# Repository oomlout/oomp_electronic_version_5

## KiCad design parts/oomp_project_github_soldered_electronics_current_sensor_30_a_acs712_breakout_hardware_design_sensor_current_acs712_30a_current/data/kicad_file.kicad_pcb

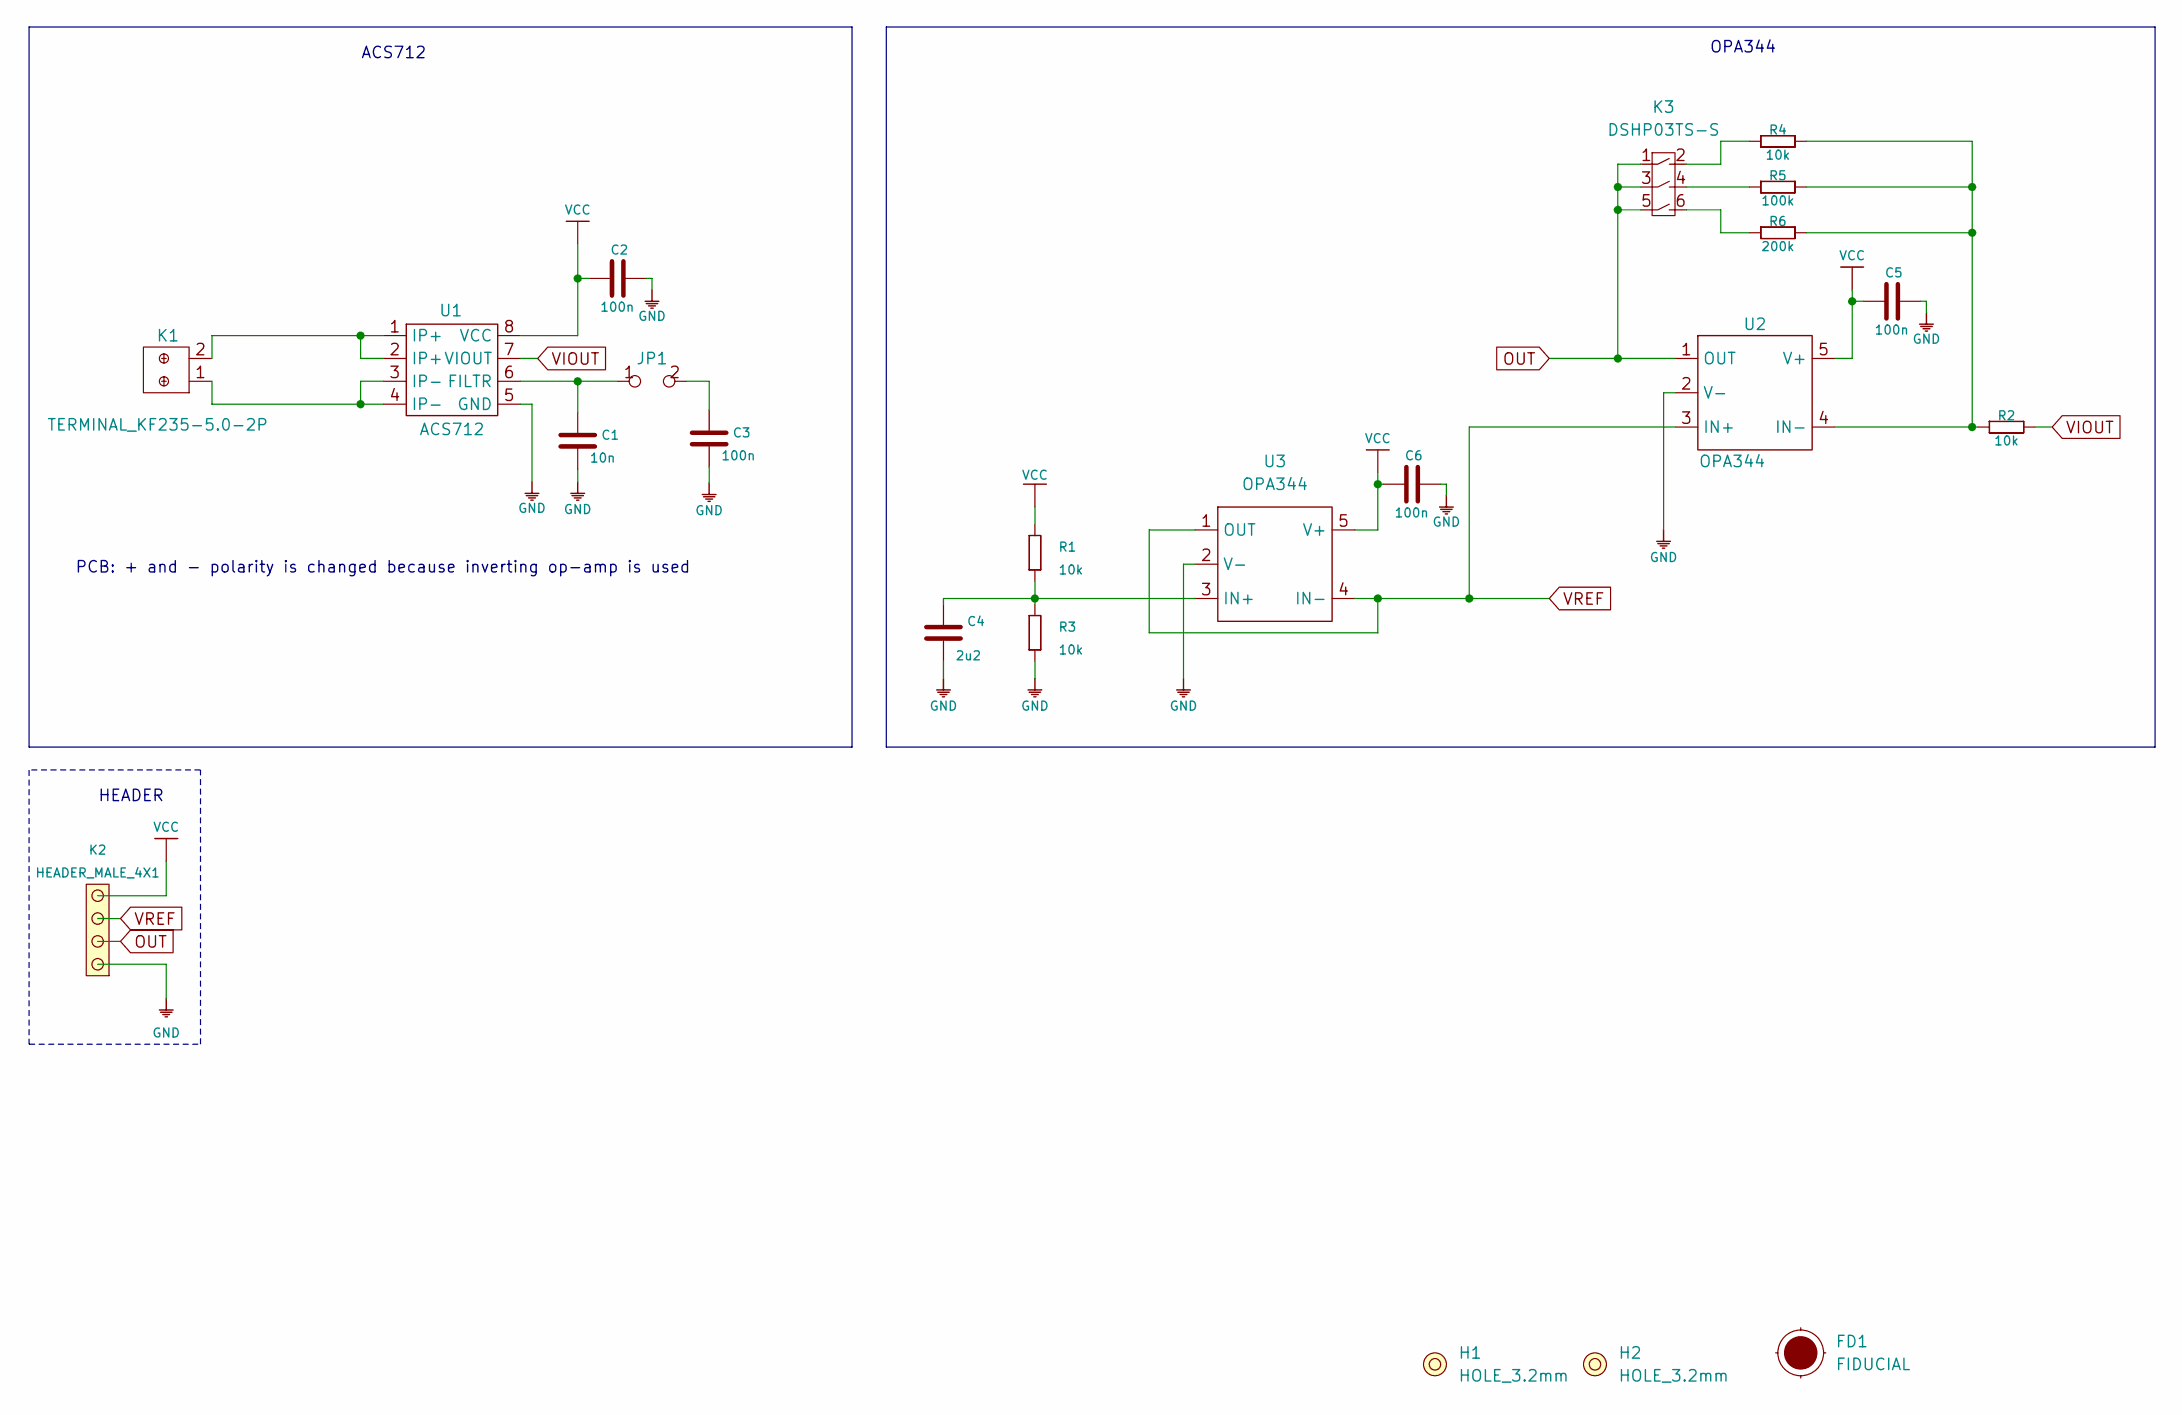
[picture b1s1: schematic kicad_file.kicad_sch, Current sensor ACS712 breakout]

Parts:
C1: 10n; 0603C
C2, C3, C5, C6: 100n; 0603C
C4: 2u2; 0603C
FD1: FIDUCIAL; FIDUCIAL_23
H1, H2: HOLE_3.2mm
JP1: SMD_JUMPER
K1: TERMINAL_KF235-5.0-2P
K2: HEADER_MALE_4X1
K3: DSHP03TS-S
R1, R2, R3, R4: 10k; 0603R
R5: 100k; 0603R
R6: 200k; 0603R
U1: ACS712; SOIC-8-SWB
U2, U3: OPA344; SOT-23-5

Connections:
GND: C1.1, C2.1, C3.1, C4.1, C5.1, C6.1, K2.1, R3.1, U1.5 (GND), U2.2 (V-), U3.2 (V-)
unnamed: C1.2, JP1.1, U1.6 (FILTR)
unnamed: C3.2, JP1.2
unnamed: C4.2, R1.1, R3.2, U3.3 (IN+)
unnamed: K1.1, U1.3 (IP-), U1.4 (IP-)
unnamed: K1.2, U1.1 (IP+), U1.2 (IP+)
unnamed: K3.2, R4.1
unnamed: K3.4, R5.1
unnamed: K3.6, R6.1
unnamed: R2.1, R4.2, R5.2, R6.2, U2.4 (IN-)
OUT: K2.2, K3.1, K3.3, K3.5, U2.1 (OUT)
VCC: C2.2, C5.2, C6.2, K2.4, R1.2, U1.8 (VCC), U2.5 (V+), U3.5 (V+)
VIOUT: R2.2, U1.7 (VIOUT)
VREF: K2.3, U2.3 (IN+), U3.1 (OUT), U3.4 (IN-)

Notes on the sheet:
ACS712
HEADER
OPA344
PCB: + and - polarity is changed because inverting op-amp is used

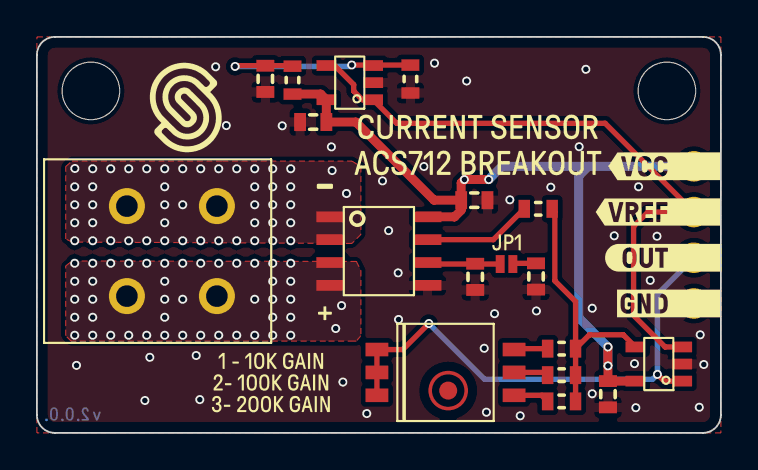
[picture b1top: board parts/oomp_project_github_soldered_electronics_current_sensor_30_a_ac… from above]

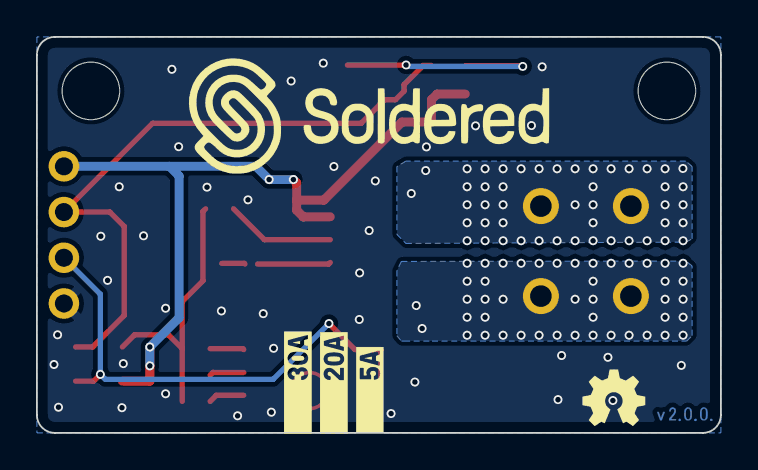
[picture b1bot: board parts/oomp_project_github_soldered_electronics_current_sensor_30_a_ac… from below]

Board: 2 copper layers, 38.0 x 22.0 mm, 37 parts (4 on the bottom side), 14 nets.

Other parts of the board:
kibuzzard-62BC34C1: G***; kibuzzard-62BC34C1
kibuzzard-62BC34F4: G***; kibuzzard-62BC34F4
kibuzzard-62BC38A6: G***; kibuzzard-62BC38A6
kibuzzard-62BC3508: G***; kibuzzard-62BC3508
kibuzzard-62BC3682: G***; kibuzzard-62BC3682
kibuzzard-62BC3718: G***; kibuzzard-62BC3718
kibuzzard-62BC3727: G***; kibuzzard-62BC3727
kibuzzard-62BC3797: G***; kibuzzard-62BC3797
kibuzzard-62BC3836: G***; kibuzzard-62BC3836
kibuzzard-62CC21A6: G***; kibuzzard-62CC21A6
kibuzzard-62CC223D: G***; kibuzzard-62CC223D
kibuzzard-62CC224E: G***; kibuzzard-62CC224E
kibuzzard-62CC2223: G***; kibuzzard-62CC2223
kibuzzard-6254242B: G***; kibuzzard-6254242B
kibuzzard-62542455: G***; kibuzzard-62542455

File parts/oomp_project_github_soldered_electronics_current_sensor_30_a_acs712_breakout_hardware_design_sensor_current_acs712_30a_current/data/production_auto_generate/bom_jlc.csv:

Comment,Designator,Footprint,LCSC Part #
100k,R5,e-radionica.com footprinti:0603R,C25803
100n,"C2,C3,C5,C6",e-radionica.com footprinti:0603C,C14663
10k,"R1,R2,R3,R4",e-radionica.com footprinti:0603R,C98220
10n,C1,e-radionica.com footprinti:0603C,C5137477
200k,R6,e-radionica.com footprinti:0603R,
2u2,C4,e-radionica.com footprinti:0603C,C23630
ACS712,U1,e-radionica.com footprinti:SOIC-8-SWB,
DSHP03TS-S,K3,e-radionica.com footprinti:DSHP03TS-S,
HEADER_MALE_4X1,K2,e-radionica.com footprinti:HEADER_MALE_4X1,C42431795
OPA344,"U2,U3",e-radionica.com footprinti:SOT-23-5,
SMD_JUMPER,JP1,e-radionica.com footprinti:SMD_JUMPER,
TERMINAL_KF235-5.0-2P,K1,e-radionica.com footprinti:TERMINAL_KF235-5.0-2P,

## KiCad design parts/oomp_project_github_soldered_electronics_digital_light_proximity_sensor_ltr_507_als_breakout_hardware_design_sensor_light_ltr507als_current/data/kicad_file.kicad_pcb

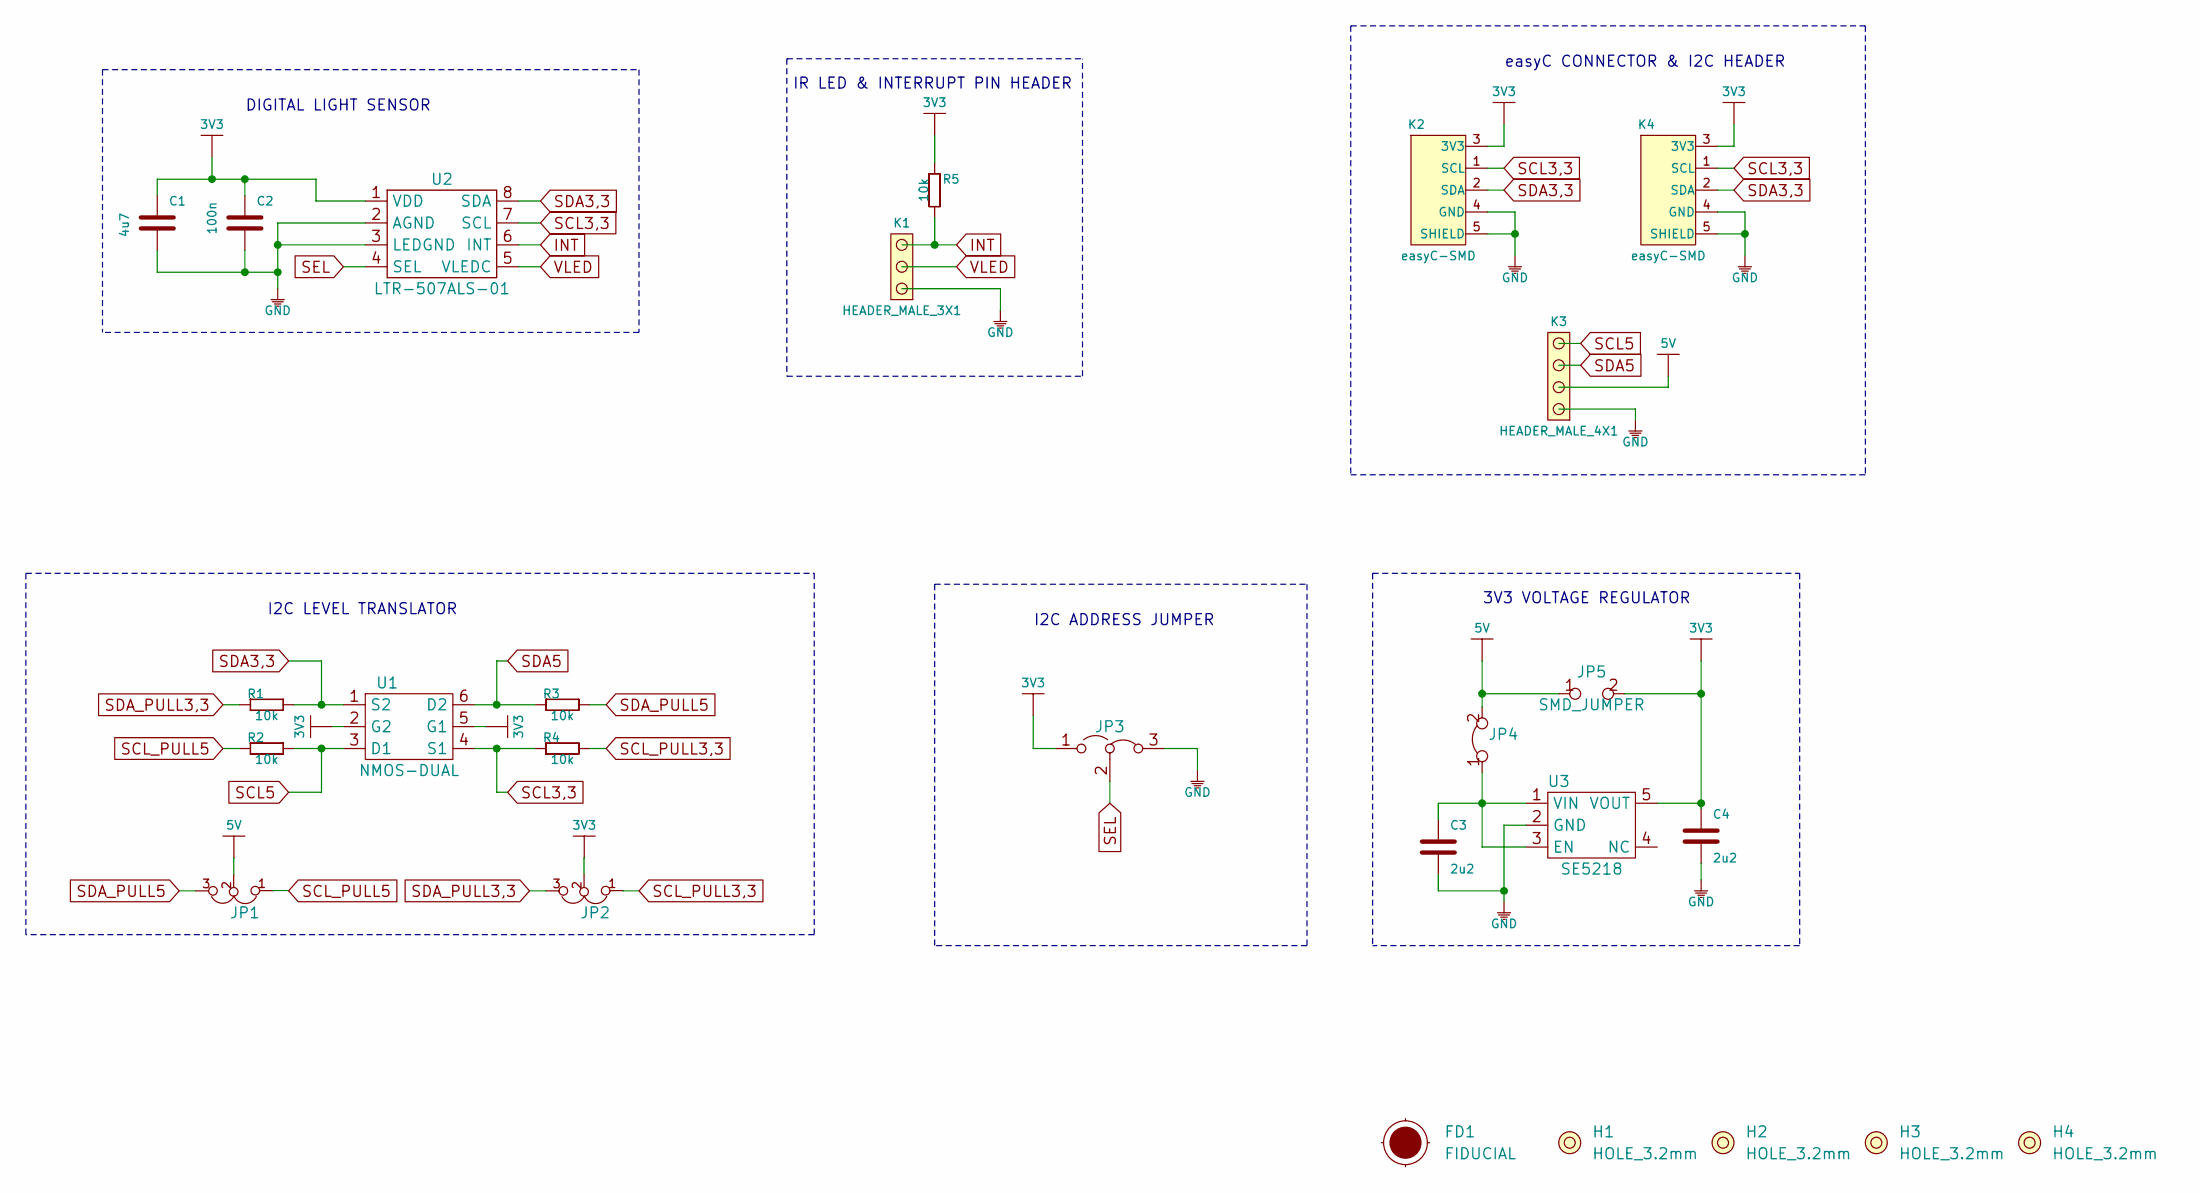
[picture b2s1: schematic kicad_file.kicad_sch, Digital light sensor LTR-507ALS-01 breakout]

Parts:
C1: 4u7; 0603C
C2: 100n; 0603C
C3, C4: 2u2; 0603C
FD1: FIDUCIAL; FIDUCIAL_23
H1, H2, H3, H4: HOLE_3.2mm
JP1, JP2: SMD_JUMPER_3_PAD_TRACE
JP3: JUMPER_3_RIGHT; SMD_JUMPER_3_PAD_CONNECTED_RIGHT
JP4: SMD-JUMPER-CONNECTED_TRACE_SLODERMASK
JP5: SMD_JUMPER
K1: HEADER_MALE_3X1
K2, K4: easyC-SMD; easyC-connector
K3: HEADER_MALE_4X1
R1, R2, R3, R4, R5: 10k; 0603R
U1: NMOS-DUAL; SOT-363
U2: LTR-507ALS-01
U3: SE5218; SOT-23-5

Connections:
3V3: C1.2, C2.2, C4.2, JP2.2, JP3.1 (A), JP5.2, K2.3 (3V3), K4.3 (3V3), R5.1, U1.2 (G2), U1.5 (G1), U2.1 (VDD), U3.5 (VOUT)
5V: JP1.2, JP4.2, JP5.1, K3.2
GND: C1.1, C2.1, C3.1, C4.1, JP3.3 (B), K1.1, K2.4 (GND), K2.5 (SHIELD), K3.1, K4.4 (GND), K4.5 (SHIELD), U2.2 (AGND), U2.3 (LEDGND), U3.2 (GND)
INT: K1.3, R5.2, U2.6 (INT)
unnamed: C3.2, JP4.1, U3.1 (VIN), U3.3 (EN)
SCL3,3: K2.1 (SCL), K4.1 (SCL), R4.1, U1.4 (S1), U2.7 (SCL)
SCL5: K3.4, R2.2, U1.3 (D1)
SCL_PULL3,3: JP2.1, R4.2
SCL_PULL5: JP1.1, R2.1
SDA3,3: K2.2 (SDA), K4.2 (SDA), R1.2, U1.1 (S2), U2.8 (SDA)
SDA5: K3.3, R3.1, U1.6 (D2)
SDA_PULL3,3: JP2.3, R1.1
SDA_PULL5: JP1.3, R3.2
SEL: JP3.2 (C), U2.4 (SEL)
VLED: K1.2, U2.5 (VLEDC)

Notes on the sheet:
IR LED & INTERRUPT PIN HEADER
easyC CONNECTOR & I2C HEADER
DIGITAL LIGHT SENSOR
I2C LEVEL TRANSLATOR
3V3 VOLTAGE REGULATOR
I2C ADDRESS JUMPER

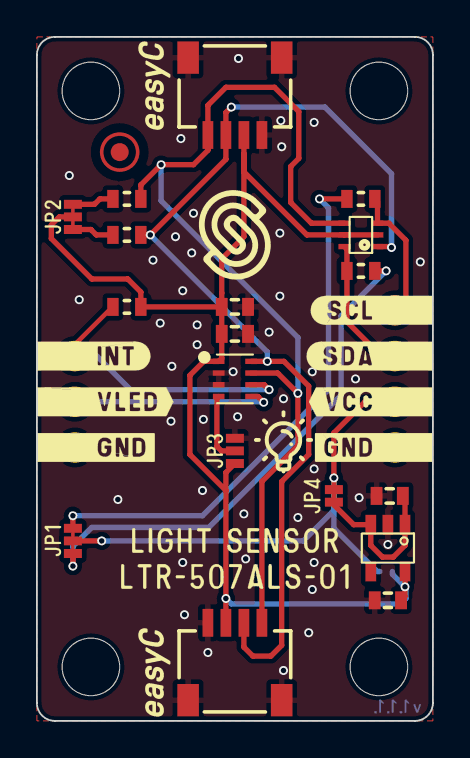
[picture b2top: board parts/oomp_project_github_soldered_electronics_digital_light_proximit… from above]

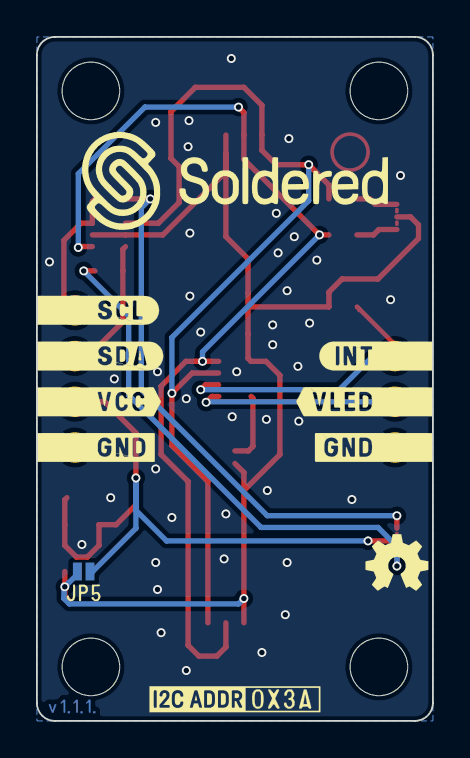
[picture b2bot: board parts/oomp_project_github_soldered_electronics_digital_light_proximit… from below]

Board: 2 copper layers, 22.0 x 38.0 mm, 26 parts (3 on the bottom side), 15 nets.

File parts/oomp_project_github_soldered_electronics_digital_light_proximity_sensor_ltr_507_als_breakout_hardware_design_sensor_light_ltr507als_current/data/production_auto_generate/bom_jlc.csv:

Comment,Designator,Footprint,LCSC Part #
100n,C2,e-radionica.com footprinti:0603C,C14663
10k,"R1,R2,R3,R4,R5",e-radionica.com footprinti:0603R,C98220
2u2,"C3,C4",e-radionica.com footprinti:0603C,C23630
4u7,C1,e-radionica.com footprinti:0603C,C69335
easyC-SMD,"K2,K4",e-radionica.com footprinti:easyC-connector,
HEADER_MALE_3X1,K1,e-radionica.com footprinti:HEADER_MALE_3X1,C49257
HEADER_MALE_4X1,K3,e-radionica.com footprinti:HEADER_MALE_4X1,C42431795
JUMPER_3_RIGHT,JP3,e-radionica.com footprinti:SMD_JUMPER_3_PAD_CONNECTED_RIGHT,
LTR-507ALS-01,U2,e-radionica.com footprinti:LTR-507ALS-01,
NMOS-DUAL,U1,e-radionica.com footprinti:SOT-363,
SE5218,U3,e-radionica.com footprinti:SOT-23-5,
SMD-JUMPER-CONNECTED_TRACE_SLODERMASK,JP4,e-radionica.com footprinti:SMD-JUMPER-CONNECTED_TRACE_SLODERMASK,
SMD_JUMPER,JP5,e-radionica.com footprinti:SMD_JUMPER,
SMD_JUMPER_3_PAD_TRACE,"JP1,JP2",e-radionica.com footprinti:SMD_JUMPER_3_PAD_TRACE,

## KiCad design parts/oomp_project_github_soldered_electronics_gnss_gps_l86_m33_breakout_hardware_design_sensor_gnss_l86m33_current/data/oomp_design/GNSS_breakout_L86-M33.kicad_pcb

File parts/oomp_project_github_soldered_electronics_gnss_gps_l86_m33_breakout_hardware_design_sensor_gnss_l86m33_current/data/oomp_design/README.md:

# OOMP KiCad design copy

Open `GNSS_breakout_L86-M33.kicad_pro` (or the `.kicad_pcb` / `.kicad_sch`) in KiCad. Local OOMP libraries are under `libraries/`. Original inputs are preserved in [../original/](../original/).

Only verified unchanged installed KiCad defaults were renamed. Modified, custom, unmatched and unavailable items remain unchanged. Soldering variants are never swapped during conversion. Existing pad coordinates, nets and UUIDs are preserved.

See [conversion_report.yaml](conversion_report.yaml) for every conversion and skip. Copy this directory before editing; regeneration refuses to overwrite edited design files.

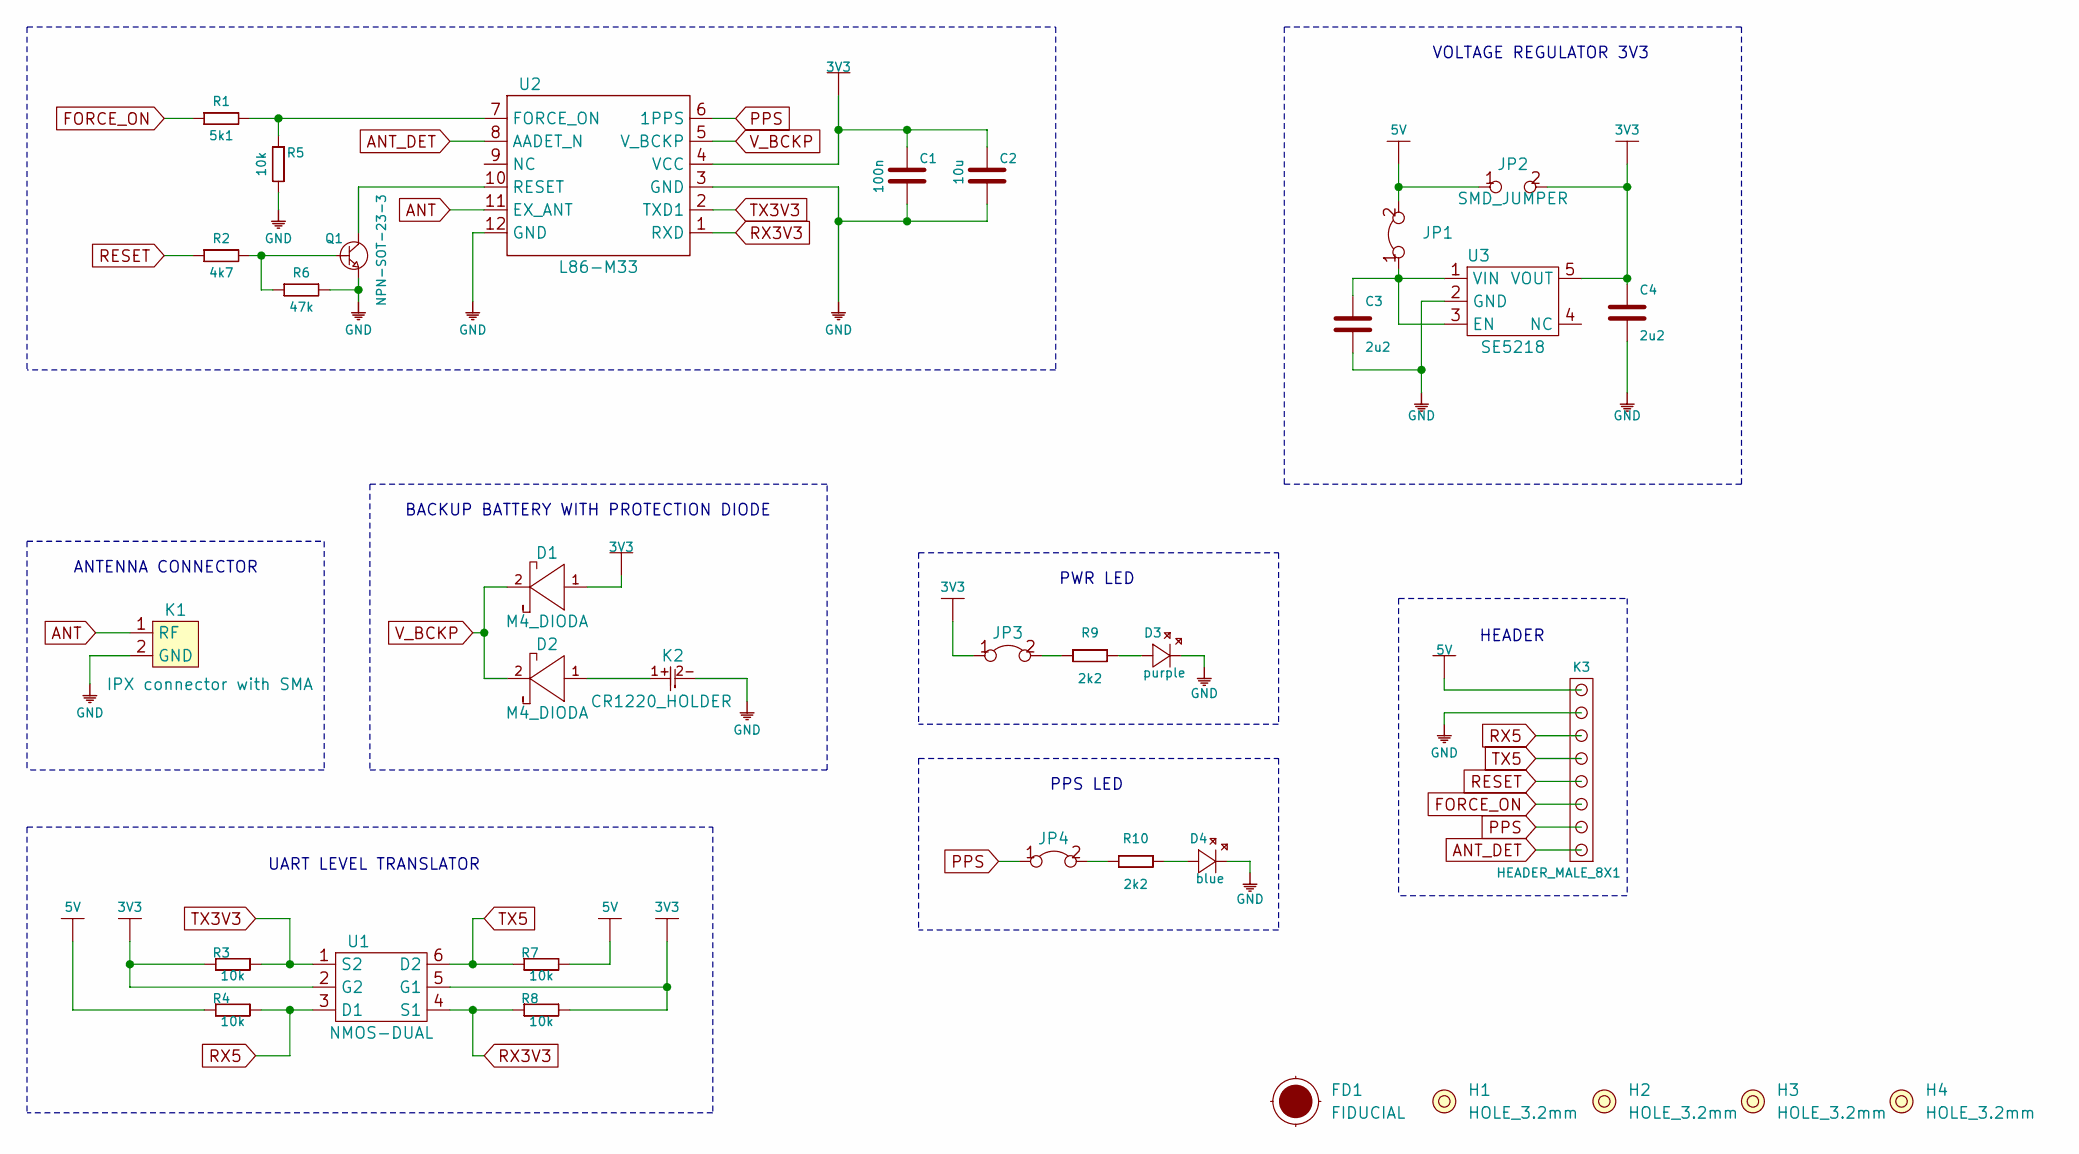
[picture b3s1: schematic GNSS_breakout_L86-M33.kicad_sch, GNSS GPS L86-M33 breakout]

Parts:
C1: 100n; 0603C
C2: 10u; 1206C
C3, C4: 2u2; 0603C
D1, D2: M4_DIODA
D3: purple; 0402LED
D4: blue; 0402LED
FD1: FIDUCIAL; FIDUCIAL_23
H1, H2, H3, H4: HOLE_3.2mm
JP1, JP3, JP4: SMD-JUMPER-CONNECTED_TRACE_SLODERMASK
JP2: SMD_JUMPER
K1: IPX connector with SMA
K2: CR1220_HOLDER
K3: HEADER_MALE_8X1
Q1: NPN-SOT-23-3; SOT-23-3
R1: 5k1; 0603R
R2: 4k7; 0603R
R3, R4, R5, R7, R8: 10k; 0603R
R6: 47k; 0603R
R9, R10: 2k2; 0402R
U1: NMOS-DUAL; SOT-363
U2: L86-M33
U3: SE5218; SOT-23-5

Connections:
3V3: C1.2, C2.2, C4.2, D1.1 (A), JP2.2, JP3.1, R3.1, R8.2, U1.2 (G2), U1.5 (G1), U2.4 (VCC), U3.5 (VOUT)
5V: JP1.2, JP2.1, K3.8, R4.1, R7.2
ANT: K1.1 (RF), U2.11 (EX_ANT)
ANT_DET: K3.1, U2.8 (AADET_N)
FORCE_ON: K3.3, R1.1
GND: C1.1, C2.1, C3.1, C4.1, D3.2 (K), D4.2 (K), K1.2 (GND), K2.2-, K3.7, Q1.2 (E), R5.2, R6.2, U2.3 (GND), U2.12 (GND), U3.2 (GND)
unnamed: C3.2, JP1.1, U3.1 (VIN), U3.3 (EN)
unnamed: D2.1 (A), K2.1+
unnamed: D3.1 (A), R9.2
unnamed: D4.1 (A), R10.2
unnamed: JP3.2, R9.1
unnamed: JP4.2, R10.1
unnamed: Q1.1 (B), R2.2, R6.1
unnamed: Q1.3 (C), U2.10 (RESET)
unnamed: R1.2, R5.1, U2.7 (FORCE_ON)
PPS: JP4.1, K3.2, U2.6 (1PPS)
RESET: K3.4, R2.1
RX3V3: R8.1, U1.4 (S1), U2.1 (RXD)
RX5: K3.6, R4.2, U1.3 (D1)
TX3V3: R3.2, U1.1 (S2), U2.2 (TXD1)
TX5: K3.5, R7.1, U1.6 (D2)
V_BCKP: D1.2 (K), D2.2 (K), U2.5 (V_BCKP)

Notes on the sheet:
ANTENNA CONNECTOR
PPS LED
VOLTAGE REGULATOR 3V3
BACKUP BATTERY WITH PROTECTION DIODE
UART LEVEL TRANSLATOR
PWR LED
HEADER

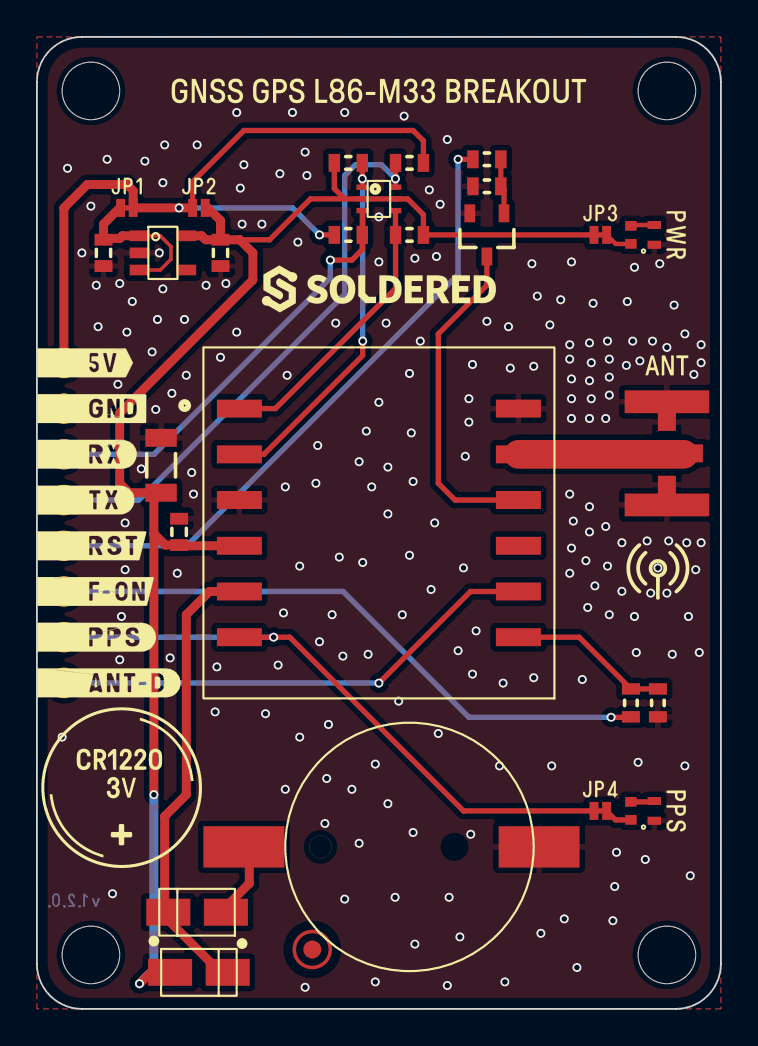
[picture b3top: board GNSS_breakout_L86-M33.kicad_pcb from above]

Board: 2 copper layers, 38.0 x 54.0 mm, 36 parts (0 on the bottom side), 22 nets.

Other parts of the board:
kibuzzard-62FB46FA: G***; kibuzzard-62FB46FA
kibuzzard-6391DAF4: G***; kibuzzard-6391DAF4

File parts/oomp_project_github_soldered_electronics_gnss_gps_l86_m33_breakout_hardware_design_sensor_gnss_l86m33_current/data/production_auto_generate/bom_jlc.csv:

Comment,Designator,Footprint,LCSC Part #
100n,C1,e-radionica.com footprinti:0603C,C14663
10k,"R3,R4,R5,R7,R8",e-radionica.com footprinti:0603R,C98220
10u,C2,e-radionica.com footprinti:1206C,
2k2,"R9,R10",e-radionica.com footprinti:0402R,C2906920
2u2,"C3,C4",e-radionica.com footprinti:0603C,C23630
47k,R6,e-radionica.com footprinti:0603R,C2907042
4k7,R2,e-radionica.com footprinti:0603R,C23162
5k1,R1,e-radionica.com footprinti:0603R,C23186
blue,D4,e-radionica.com footprinti:0402LED,C434447
CR1220_HOLDER,K2,e-radionica.com footprinti:CR1220_HOLDER,
HEADER_MALE_8X1,K3,e-radionica.com footprinti:HEADER_MALE_8X1,C492421
IPX connector with SMA,K1,e-radionica.com footprinti:IPX connector with SMA,
L86-M33,U2,e-radionica.com footprinti:L86-M33,
M4_DIODA,"D1,D2",e-radionica.com footprinti:M4_DIODA,
NMOS-DUAL,U1,e-radionica.com footprinti:SOT-363,
NPN-SOT-23-3,Q1,e-radionica.com footprinti:SOT-23-3,
purple,D3,e-radionica.com footprinti:0402LED,
SE5218,U3,e-radionica.com footprinti:SOT-23-5,
SMD-JUMPER-CONNECTED_TRACE_SLODERMASK,"JP1,JP3,JP4",e-radionica.com footprinti:SMD-JUMPER-CONNECTED_TRACE_SLODERMASK,
SMD_JUMPER,JP2,e-radionica.com footprinti:SMD_JUMPER,

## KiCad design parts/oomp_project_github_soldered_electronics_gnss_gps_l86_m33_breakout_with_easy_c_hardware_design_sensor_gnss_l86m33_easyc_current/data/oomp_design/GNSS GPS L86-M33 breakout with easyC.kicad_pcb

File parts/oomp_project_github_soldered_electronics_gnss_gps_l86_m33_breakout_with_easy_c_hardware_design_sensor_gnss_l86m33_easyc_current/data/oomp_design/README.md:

# OOMP KiCad design copy

Open `GNSS GPS L86-M33 breakout with easyC.kicad_pro` (or the `.kicad_pcb` / `.kicad_sch`) in KiCad. Local OOMP libraries are under `libraries/`. Original inputs are preserved in [../original/](../original/).

Only verified unchanged installed KiCad defaults were renamed. Modified, custom, unmatched and unavailable items remain unchanged. Soldering variants are never swapped during conversion. Existing pad coordinates, nets and UUIDs are preserved.

See [conversion_report.yaml](conversion_report.yaml) for every conversion and skip. Copy this directory before editing; regeneration refuses to overwrite edited design files.

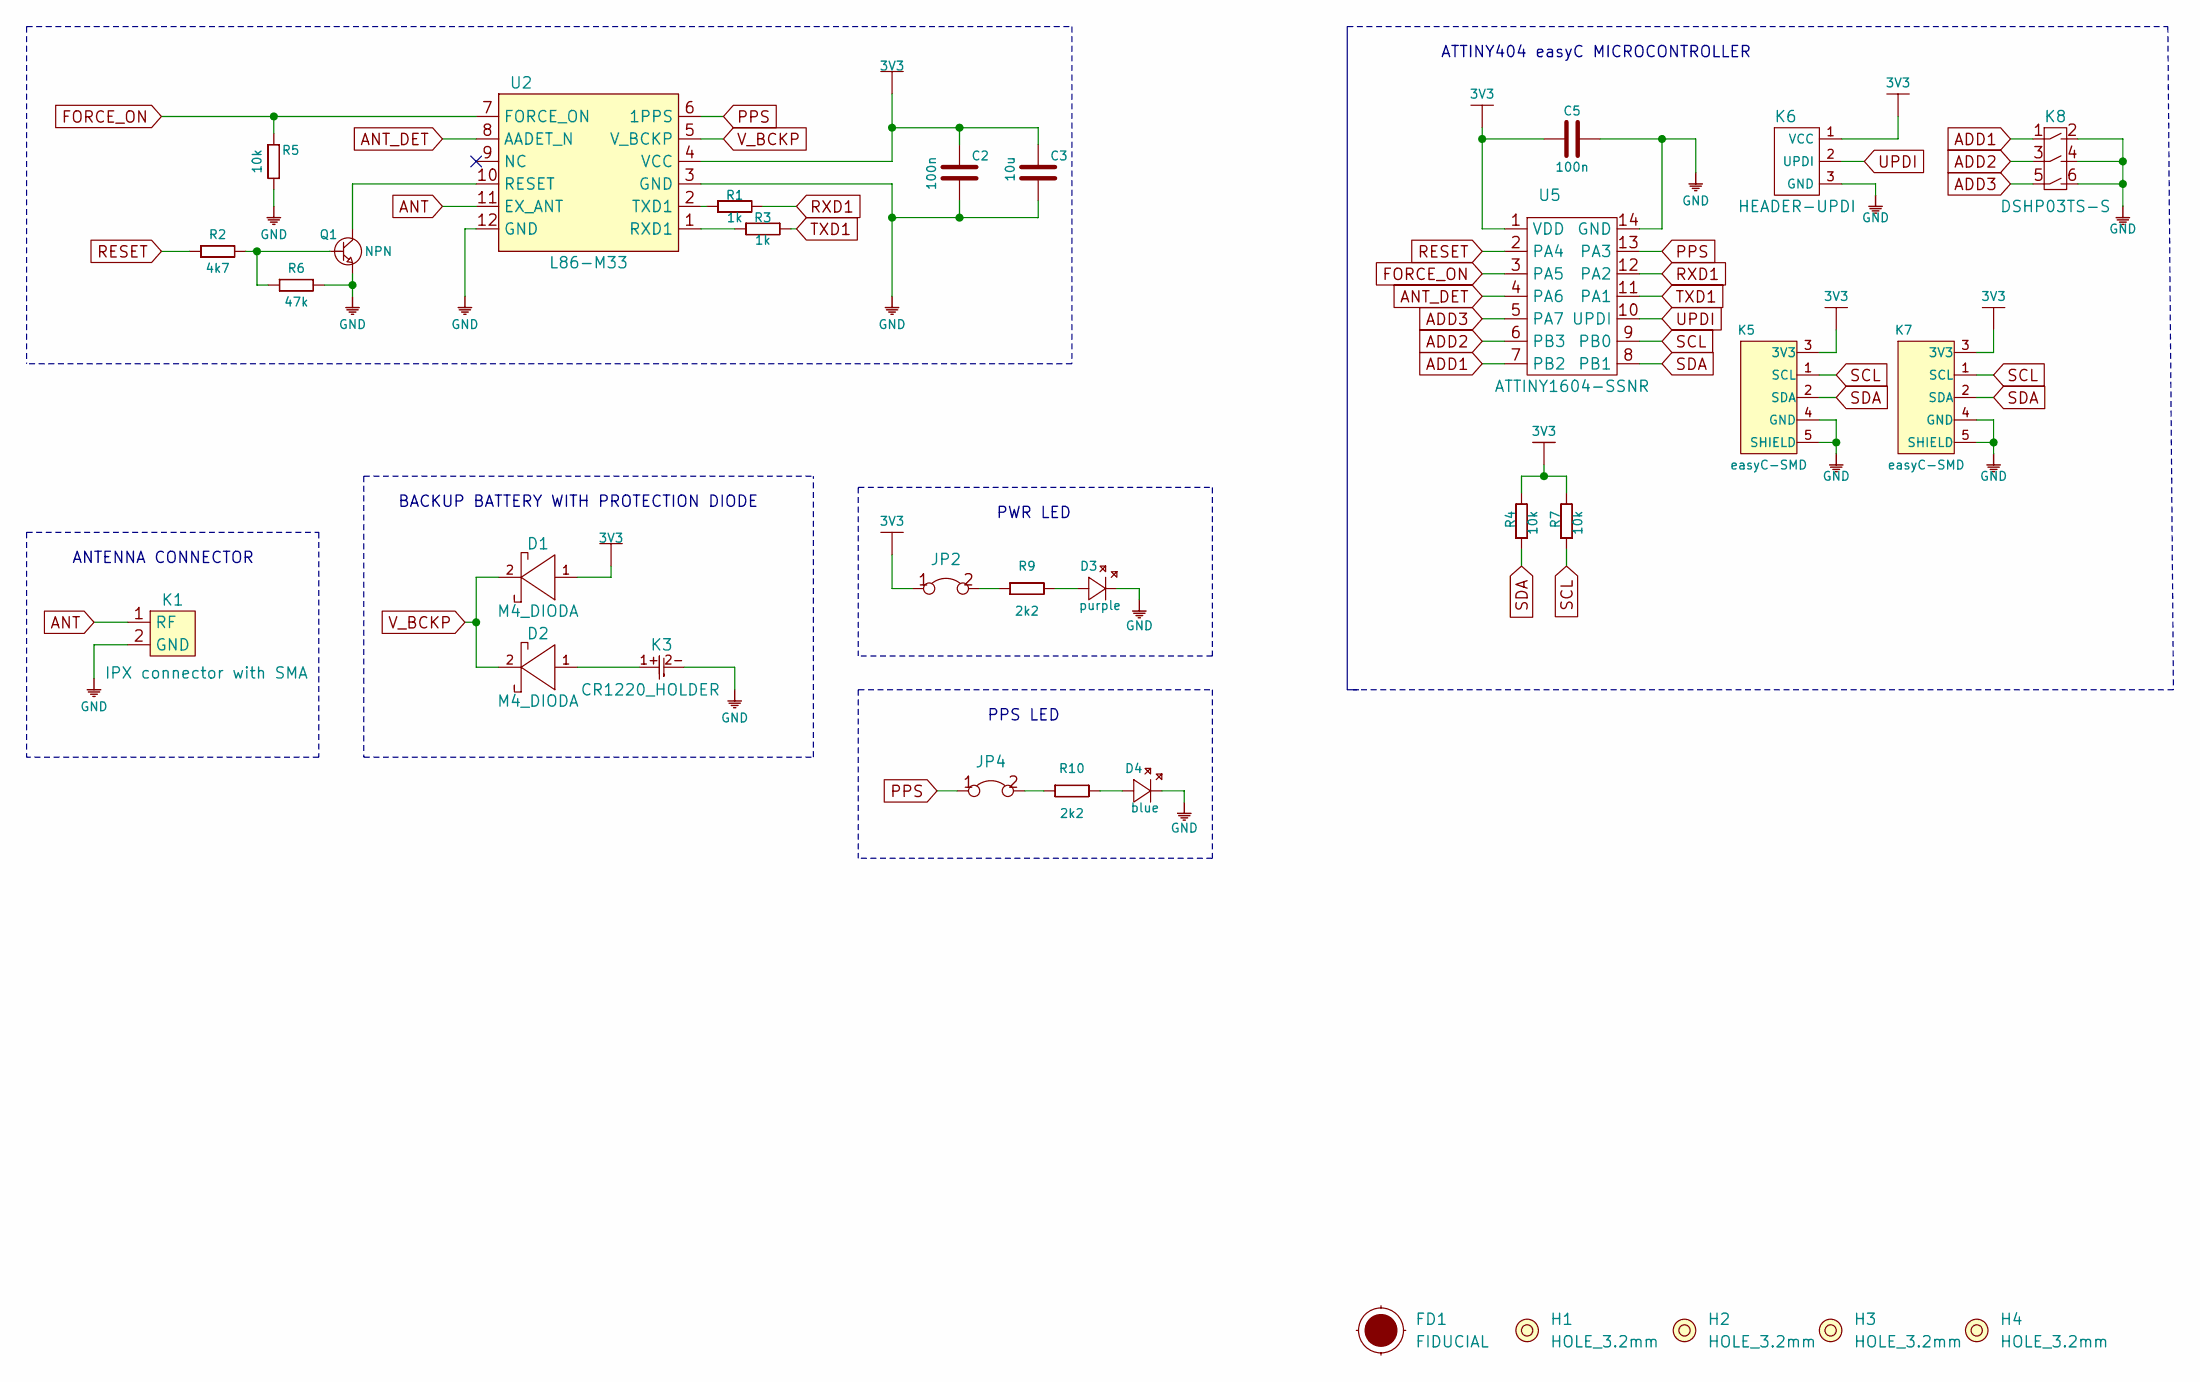
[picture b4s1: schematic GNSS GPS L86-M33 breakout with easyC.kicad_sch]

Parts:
C2, C5: 100n; 0603C
C3: 10u; 1206C
D1, D2: M4_DIODA
D3: purple; 0402LED
D4: blue; 0402LED
FD1: FIDUCIAL; FIDUCIAL_23
H1, H2, H3, H4: HOLE_3.2mm
JP2, JP4: SMD-JUMPER-CONNECTED_TRACE_SOLDERMASK
K1: IPX connector with SMA
K3: CR1220_HOLDER
K5, K7: easyC-SMD; easyC-connector
K6: HEADER-UPDI
K8: DSHP03TS-S
Q1: NPN; SOT-23-3
R1, R3: 1k; 0603R
R2: 4k7; 0603R
R4, R5, R7: 10k; 0603R
R6: 47k; 0603R
R9, R10: 2k2; 0402R
U2: L86-M33
U5: ATTINY1604-SSNR; SOIC-14

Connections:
3V3: C2.2, C3.2, C5.1, D1.1 (A), JP2.1, K5.3 (3V3), K6.1 (VCC), K7.3 (3V3), R4.2, R7.2, U2.4 (VCC), U5.1 (VDD)
ADD1: K8.1, U5.7 (PB2)
ADD2: K8.3, U5.6 (PB3)
ADD3: K8.5, U5.5 (PA7)
ANT: K1.1 (RF), U2.11 (EX_ANT)
ANT_DET: U2.8 (AADET_N), U5.4 (PA6)
FORCE_ON: R5.1, U2.7 (FORCE_ON), U5.3 (PA5)
GND: C2.1, C3.1, C5.2, D3.2 (K), D4.2 (K), K1.2 (GND), K3.2-, K5.4 (GND), K5.5 (SHIELD), K6.3 (GND), K7.4 (GND), K7.5 (SHIELD), K8.2, K8.4, K8.6, Q1.2 (E), R5.2, R6.2, U2.3 (GND), U2.12 (GND), U5.14 (GND)
unnamed: D2.1 (A), K3.1+
unnamed: D3.1 (A), R9.2
unnamed: D4.1 (A), R10.2
unnamed: JP2.2, R9.1
unnamed: JP4.2, R10.1
unnamed: Q1.1 (B), R2.2, R6.1
unnamed: Q1.3 (C), U2.10 (RESET)
unnamed: R1.1, U2.2 (TXD1)
unnamed: R3.1, U2.1 (RXD1)
PPS: JP4.1, U2.6 (1PPS), U5.13 (PA3)
RESET: R2.1, U5.2 (PA4)
RXD1: R1.2, U5.12 (PA2)
SCL: K5.1 (SCL), K7.1 (SCL), R7.1, U5.9 (PB0)
SDA: K5.2 (SDA), K7.2 (SDA), R4.1, U5.8 (PB1)
TXD1: R3.2, U5.11 (PA1)
UPDI: K6.2 (UPDI), U5.10 (UPDI)
V_BCKP: D1.2 (K), D2.2 (K), U2.5 (V_BCKP)

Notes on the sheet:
PPS LED
BACKUP BATTERY WITH PROTECTION DIODE
ATTINY404 easyC MICROCONTROLLER
ANTENNA CONNECTOR
PWR LED

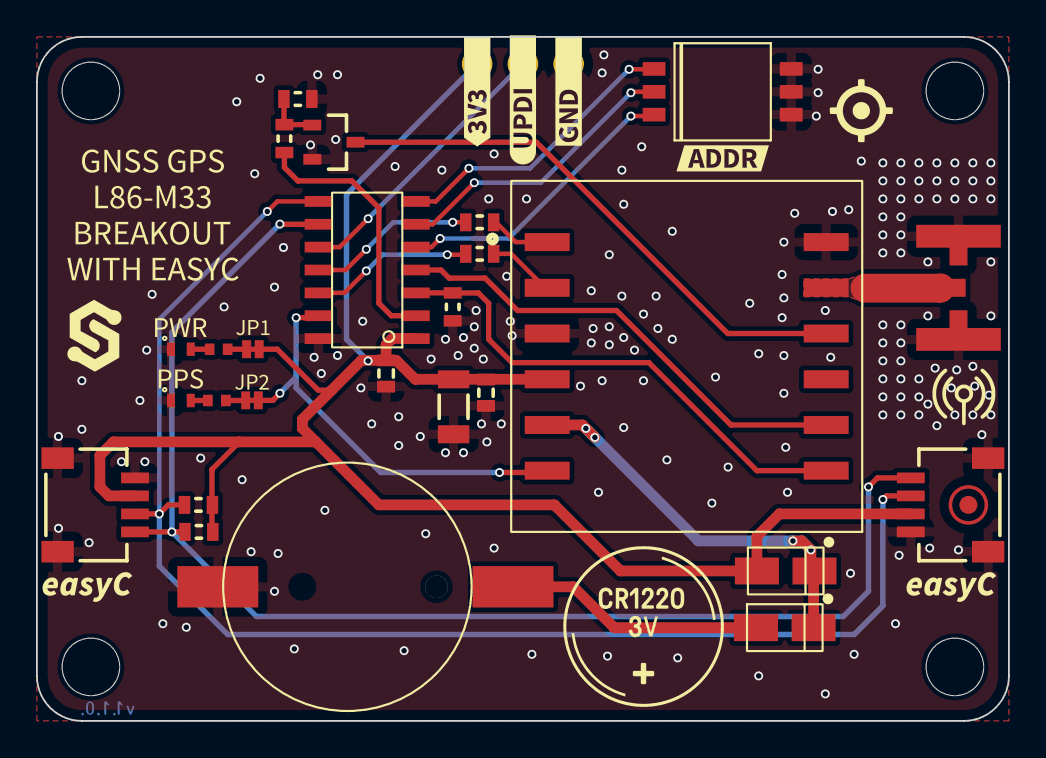
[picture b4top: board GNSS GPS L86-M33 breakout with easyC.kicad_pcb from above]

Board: 2 copper layers, 54.0 x 38.0 mm, 45 parts (1 on the bottom side), 25 nets.

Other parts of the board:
Ref**: Val**; Version1.1.0
kibuzzard-646B10BE: G***; kibuzzard-646B10BE
kibuzzard-646B10CD: G***; kibuzzard-646B10CD
kibuzzard-646B10D8: G***; kibuzzard-646B10D8
kibuzzard-646B10E4: G***; kibuzzard-646B10E4
kibuzzard-646B110E: G***; kibuzzard-646B110E
kibuzzard-646B122B: G***; kibuzzard-646B122B
kibuzzard-646B123E: G***; kibuzzard-646B123E
kibuzzard-646B1119: G***; kibuzzard-646B1119
kibuzzard-646B1126: G***; kibuzzard-646B1126
kibuzzard-646B1134: G***; kibuzzard-646B1134
kibuzzard-646B1202: G***; kibuzzard-646B1202
kibuzzard-646B1217: G***; kibuzzard-646B1217

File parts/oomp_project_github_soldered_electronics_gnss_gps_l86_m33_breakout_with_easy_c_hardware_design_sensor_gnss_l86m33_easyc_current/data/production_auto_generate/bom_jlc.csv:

Comment,Designator,Footprint,LCSC Part #
100n,"C2,C5",e-radionica.com footprinti:0603C,C14663
10k,"R4,R5,R7",e-radionica.com footprinti:0603R,C98220
10u,C3,e-radionica.com footprinti:1206C,
1k,"R1,R3",e-radionica.com footprinti:0603R,C2907002
2k2,"R9,R10",e-radionica.com footprinti:0402R,C2906920
47k,R6,e-radionica.com footprinti:0603R,C2907042
4k7,R2,e-radionica.com footprinti:0603R,C23162
ATTINY1604-SSNR,U5,e-radionica.com footprinti:SOIC-14,
blue,D4,e-radionica.com footprinti:0402LED,C434447
CR1220_HOLDER,K3,e-radionica.com footprinti:CR1220_HOLDER,
DSHP03TS-S,K8,e-radionica.com footprinti:DSHP03TS-S,
easyC-SMD,"K5,K7",e-radionica.com footprinti:easyC-connector,
HEADER-UPDI,K6,e-radionica.com footprinti:HEADER-UPDI,C49257
IPX connector with SMA,K1,e-radionica.com footprinti:IPX connector with SMA,
L86-M33,U2,e-radionica.com footprinti:L86-M33,
M4_DIODA,"D1,D2",e-radionica.com footprinti:M4_DIODA,
NPN,Q1,e-radionica.com footprinti:SOT-23-3,
purple,D3,e-radionica.com footprinti:0402LED,
SMD-JUMPER-CONNECTED_TRACE_SOLDERMASK,"JP2,JP4",e-radionica.com footprinti:SMD-JUMPER-CONNECTED_TRACE_SOLDERMASK,
